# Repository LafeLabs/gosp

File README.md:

# gosp
Geometron Optical Serial Protocol

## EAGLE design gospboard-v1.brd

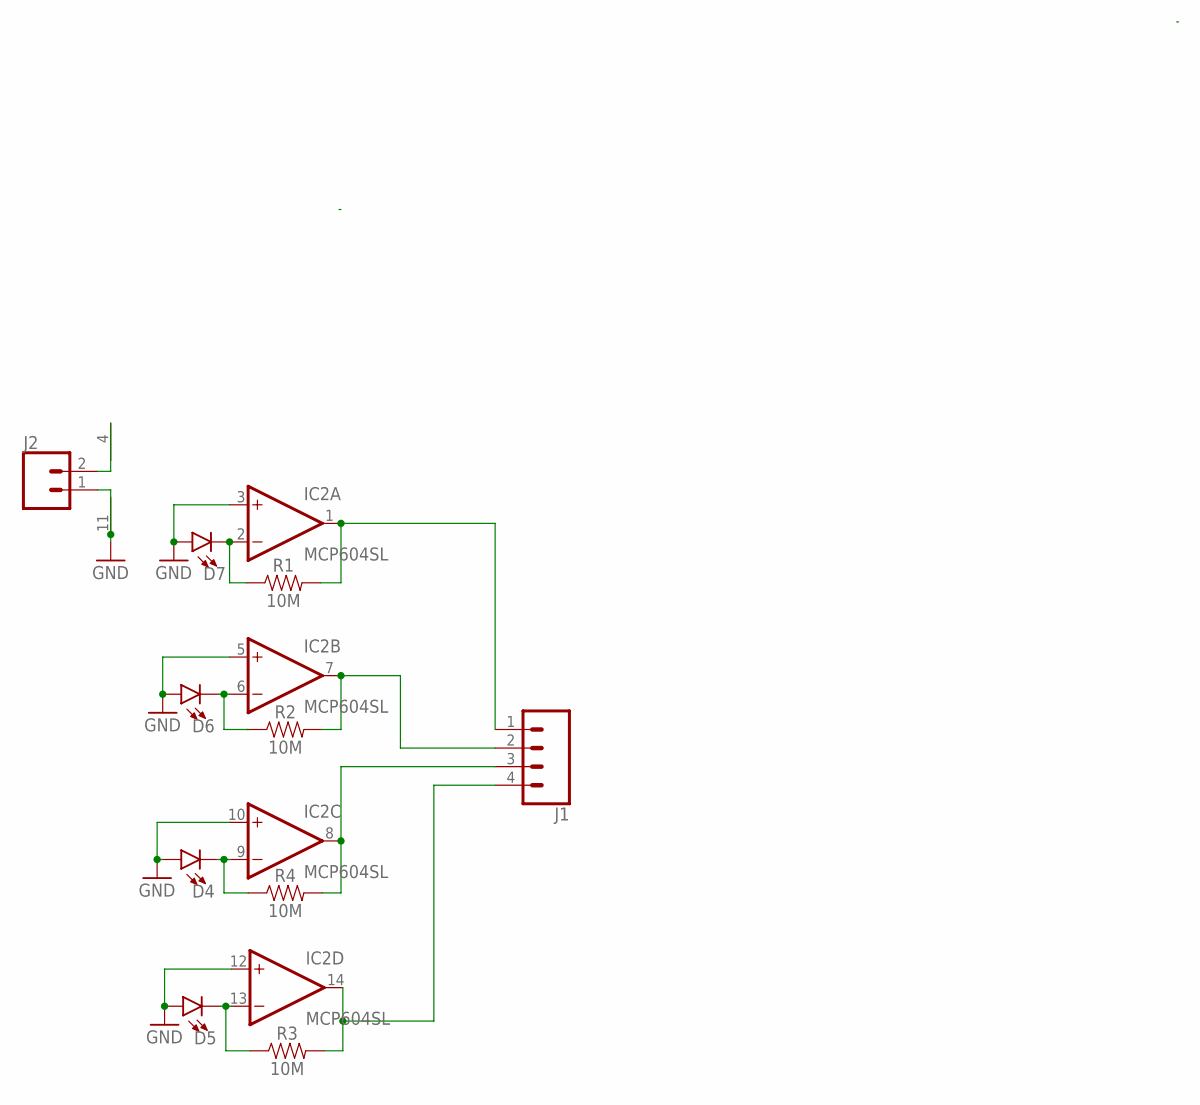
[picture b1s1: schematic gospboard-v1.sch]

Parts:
D4, D5, D6, D7: LED3MM; LED_3MM
IC2: MCP604SL; SO14
J1: CONN_04; 1X04
J2: CONN_02; 1X02
R1, R2, R3, R4: 10M; 0603

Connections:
GND: D4.A, D5.A, D6.A, D7.A, IC2.3 (+IN), IC2.5 (+IN), IC2.10 (+IN), IC2.11 (V-), IC2.12 (+IN), J2.1
unnamed: D7.K (C), IC2.2 (-IN), R1.1
unnamed: IC2.8 (OUT), J1.3, R4.2
unnamed: D6.K (C), IC2.6 (-IN), R2.1
unnamed: D4.K (C), IC2.9 (-IN), R4.1
unnamed: IC2.7 (OUT), J1.2, R2.2
unnamed: IC2.14 (OUT), J1.4, R3.2
unnamed: D5.K (C), IC2.13 (-IN), R3.1
unnamed: IC2.4 (V+), J2.2
PIN1: IC2.1 (OUT), J1.1, R1.2

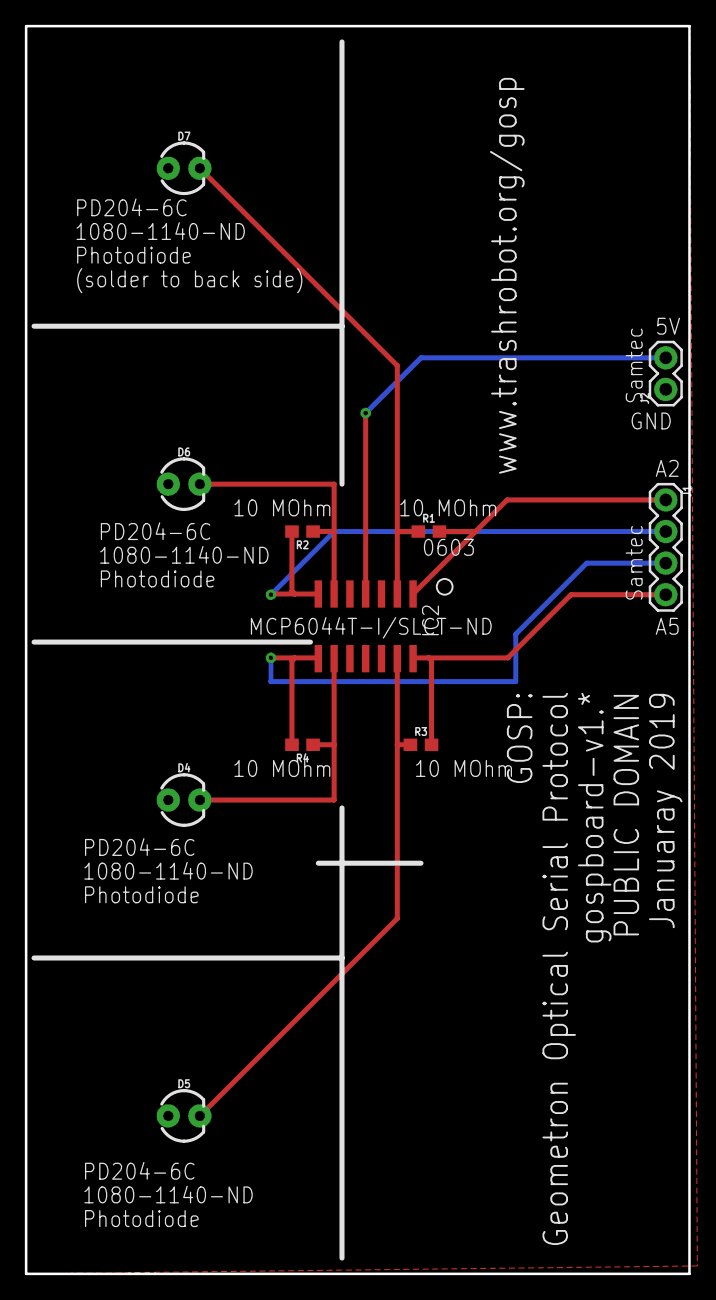
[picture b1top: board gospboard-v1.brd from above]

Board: 2 copper layers, 53.3 x 100.3 mm, 11 parts (0 on the bottom side), 10 nets.

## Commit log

2019-01-27 moved gosp files into github repo
2019-01-27 added web page code and arduino code
2019-01-27 made webcode work as small standalone page
2019-01-27 added dna which was missing due to error in dnagenerator.php
2019-01-29 added enable bit on beginning and end of overall signal, and extended byte bit over the thing
2019-01-29 arduino now reads a string and puts it down serial line in gosp_ascii_serial.ino
2019-01-31 added a hardware enable switch and some labels

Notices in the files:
gospboard-v1.brd:
PUBLIC DOMAIN
parts and their libraries:
SparkFun-LED: Licensing: Creative Commons ShareAlike 4.0 International - https://creativecommons.org/licenses/by-sa/4.0
